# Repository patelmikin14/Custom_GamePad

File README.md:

**GamePad. End-to-End PCB Design in KiCad**

Custom Symbols · Footprint Engineering · DRC/ERC · IPC-Compliant Output · Gerber Package

A full PCB design project executed entirely in KiCad, from blank schematic through to manufacturer-ready Gerber files. Every decision was made with manufacturing constraints and industry standards in mind.

**1. Schematic design & library familiarization**
Before opening KiCad, I reviewed the full circuit on paper, mapping every signal path, power rail, and component dependency. This offline pass was intentional: it forces architectural thinking before you get distracted by the software. The schematic was then rebuilt from scratch in KiCad's Schematic Editor using standard component symbols from the pre-installed libraries and power symbols for VCC, GND, and regulated supply nets.
Every component was assigned a reference designator, value, and where applicable, a part number. Net labels replaced physical wire routing between distant schematic blocks, keeping the design readable and reconfigurable, a practice consistent with schematic documentation quality expectations outlined in IPC-2612 (schematic documentation requirements for PCBs).
Net integrity was verified at each stage, every pin was either driven, pulled, or deliberately left floating with intent documented.

**2. ERC. Catching errors at the source**
The Electrical Rules Check was run incrementally throughout schematic construction, not just at the end. Every time a new block of components was wired in, ERC was triggered immediately to surface conflicts: unconnected pins, conflicting drive types, missing power flags, duplicate reference designators. Addressing these at the component level is significantly faster than untangling a full-schematic error list at completion.
Common flags addressed included missing PWR_FLAG symbols on power nets, pin type mismatches on passive components, and unconnected input pins on logic devices. Each was resolved with an understanding of why the rule exists, not suppressed. This incremental verification approach mirrors the design review philosophy embedded in IPC-2221B (Generic Standard on Printed Board Design), which emphasizes design validation at each stage of the process rather than a single end-of-cycle check.

**3. Custom symbol creation. The OLED module**
The OLED display module required for this design was not available in the KiCad symbol libraries. Rather than approximating with a generic connector symbol, a shortcut that might cause footprint mismatches downstream, I built a custom symbol using the KiCad Symbol Editor.
Every pin was defined with the correct electrical type: power, ground, bidirectional (SDA), input (SCL), and reset. Pin electrical types directly affect ERC validation, an incorrectly typed pin can mask real drive conflicts or generate false errors that obscure genuine issues. The symbol was drawn to reflect the module's physical block structure, making the interface immediately readable to anyone reviewing the schematic.
The symbol was saved to a project-local library to ensure portability and prevent dependency on global library versions, a practice aligned with IPC-2612 documentation control guidelines.

**4. Footprint assignment, cross-referencing datasheets and distributors**
For each unique component, I cross-referenced three sources: the KiCad footprint library, the manufacturer datasheet (specifically the mechanical drawing and recommended land pattern), and distributor listings on Mouser to confirm stock and lead time. Land pattern dimensions were validated against IPC-7351C (Land Pattern Standard for SMD Components), which defines pad size, pitch tolerance, and courtyard clearance requirements for each component package type.
Footprint selection criteria applied throughout:
•	Package pitch confirmed against manufacturer soldering capability, fine-pitch components below 0.5mm were flagged for assembly risk assessment
•	Courtyard boundaries set to IPC-7351C minimums to prevent component overlap and ensure rework access
•	Through-hole vs. SMD selection weighed against assembly method, rework accessibility, and wave vs. reflow process compatibility
•	Component availability and lifecycle status checked at point of footprint assignment and not after layout
Where two parts were electrically equivalent and mechanically compatible, the lower-cost, higher-availability option was selected. A part that goes out of stock kills a production run and availability is a DFM consideration as much as geometry is.

**5. Custom footprint creation. The two non-standard parts**
Two non-standard components had no adequate footprint match in the KiCad library. Both were built from scratch using the Footprint Editor, working directly from the mechanical drawing in each component's datasheet. Land patterns were constructed in accordance with IPC-7351C guidelines, pad geometries, courtyard expansion, and fabrication layer outlines all derived from the standard's requirements for the applicable package type.
•	Copper pads: Pad size and position from the IPC-7351C recommended land pattern; SMD pads assigned to F.Cu, through-hole pads with drill diameter set to pin diameter plus IPC-recommended annular ring allowance
•	Drill holes: Diameter set per IPC-2221B minimum annular ring requirements to ensure structural integrity post-fabrication
•	Silkscreen (F.Silkscreen): Component outline and pin marker placed per IPC-7351C, offset from pad edges to remain visible post-solder
•	Courtyard (F.Courtyard): Clearance boundary set to IPC-7351C Level B minimums
•	Fabrication layer (F.Fab): True component body outline for assembly documentation and pick-and-place reference
Both footprints were verified by overlaying the 3D model and checking pad positions against the datasheet mechanical drawing before use in the layout.

**6. Manufacturer selection and constraint mapping**
The manufacturer was selected before layout began. The manufacturer's published design rules were loaded into KiCad's Board Setup and cross-checked against the minimum electrical spacing and conductor width requirements defined in IPC-2221B. Where the manufacturer's tolerances were tighter than IPC minimums, the manufacturer's values were used, the tighter constraint always governs.
•	Minimum trace width, set per manufacturer capability, validated against IPC-2221B Table 6-1 current-carrying capacity requirements for the copper weight selected
•	Minimum clearance confirmed against IPC-2221B electrical spacing tables for the board's operating voltage class
•	Minimum drill size & annular ring set to manufacturer capability, checked against IPC-2221B minimum annular ring requirements for the applicable hole class
•	Board edge clearance, copper keepout applied at the manufacturer's specified margin from Edge.Cuts
•	Copper weight selected against current load requirements using IPC-2221B trace width/current tables
All values were entered as hard constraints in KiCad so DRC would automatically flag violations during layout, no relying on manual checks after the fact.

**7. PCB layout and routing**
Component placement was tackled first, grouping by functional block (power, MCU, display, input) and positioning decoupling capacitors as close to IC power pins as physically possible. Placement decisions were made with assembly in mind: components on the same side, orientation standardised to simplify pick-and-place programming, and fine-pitch parts kept away from board edges to reduce handling risk during manufacturing practices consistent with IPC-A-610 acceptability criteria for component placement quality.
•	Power traces routed wider than signal traces, sized to current requirements using IPC-2221B trace width tables
•	Vias sized to manufacturer minimums with annular rings meeting IPC-2221B Class B requirements
•	45° routing angles used throughout, 90° corners create acid traps during etching and are explicitly flagged in IPC-2221B
•	Ground pours added on back copper to provide low-impedance return paths and reduce EMI coupling
•	I²C signal traces kept short and separated from switching power nets to reduce crosstalk
Ground pour was applied last after all routing was complete, with thermal reliefs on through-hole pads to ensure reliable solder joint formation, a direct J-STD-001 (Requirements for Soldering Electrical and Electronic Assemblies) consideration, which specifies acceptable heat transfer conditions for through-hole soldering.

**8. DRC. Validating against the standard before files leave**
The full Design Rules Check was run against the manufacturer constraints loaded in Board Setup, every copper feature on every layer validated simultaneously for clearance violations, unconnected nets, acid trap geometries, silkscreen-to-pad overlap, missing courtyard definitions, and drill-to-copper clearances.
No DRC flag was suppressed without a deliberate, documented reason. This is the point where DFM intent gets validated at the physical level and it maps directly to the pre-fabrication review process described in IPC-2221B. Silkscreen was checked to ensure no markings overlapped exposed copper pads, which would compromise solder mask inspection per IPC-A-610 visual acceptability criteria.
DRC was run multiple times as final refinements were made. A clean DRC result against real manufacturer constraints, not default KiCad tolerances was the gate condition for moving to Gerber generation.

**9. BOM generation and Gerber output**
The Bill of Materials was exported with full component attributes, reference designator, value, footprint, manufacturer part number, and quantity structured to be directly usable by a procurement or assembly team without requiring follow-up clarification.
The surface finish (HASL vs. ENIG) was selected with solderability in mind, ENIG provides a flatter, more consistent surface for fine-pitch components, which J-STD-001 identifies as a factor in achieving acceptable solder joint formation.
The full Gerber package generated:
•	F.Cu / B.Cu - front and back copper layers
•	F.Mask / B.Mask - solder mask layers defining exposed pad areas
•	F.Silkscreen / B.Silkscreen - component labels and board markings
•	Edge.Cuts - board outline for routing and panelisation
•	Drill file (.drl / Excellon format) - all via and through-hole positions and diameters
All files were verified in a Gerber viewer prior to upload, checking layer alignment, aperture definitions, and drill file integrity. The package was then submitted to the manufacturer portal where board specifications were finalised: material (FR-4), copper weight, surface finish, solder mask colour, silkscreen, and controlled impedance requirements where applicable.

**Standards Referenced:**

IPC-2221B - Generic PCB Design Standard (clearances, drill, annular ring, trace sizing)

IPC-A-610 - Acceptability of Electronic Assemblies (placement, solder joint, silkscreen criteria)

J-STD-001 - Soldering Requirements (thermal relief, paste aperture, surface finish)

IPC-2612 - Schematic Documentation Requirements

**Tools Used**

KiCad · Symbol Editor · Footprint Editor · ERC / DRC · Gerber / Excellon output · Mouser / DigiKey component validation · Gerber viewer

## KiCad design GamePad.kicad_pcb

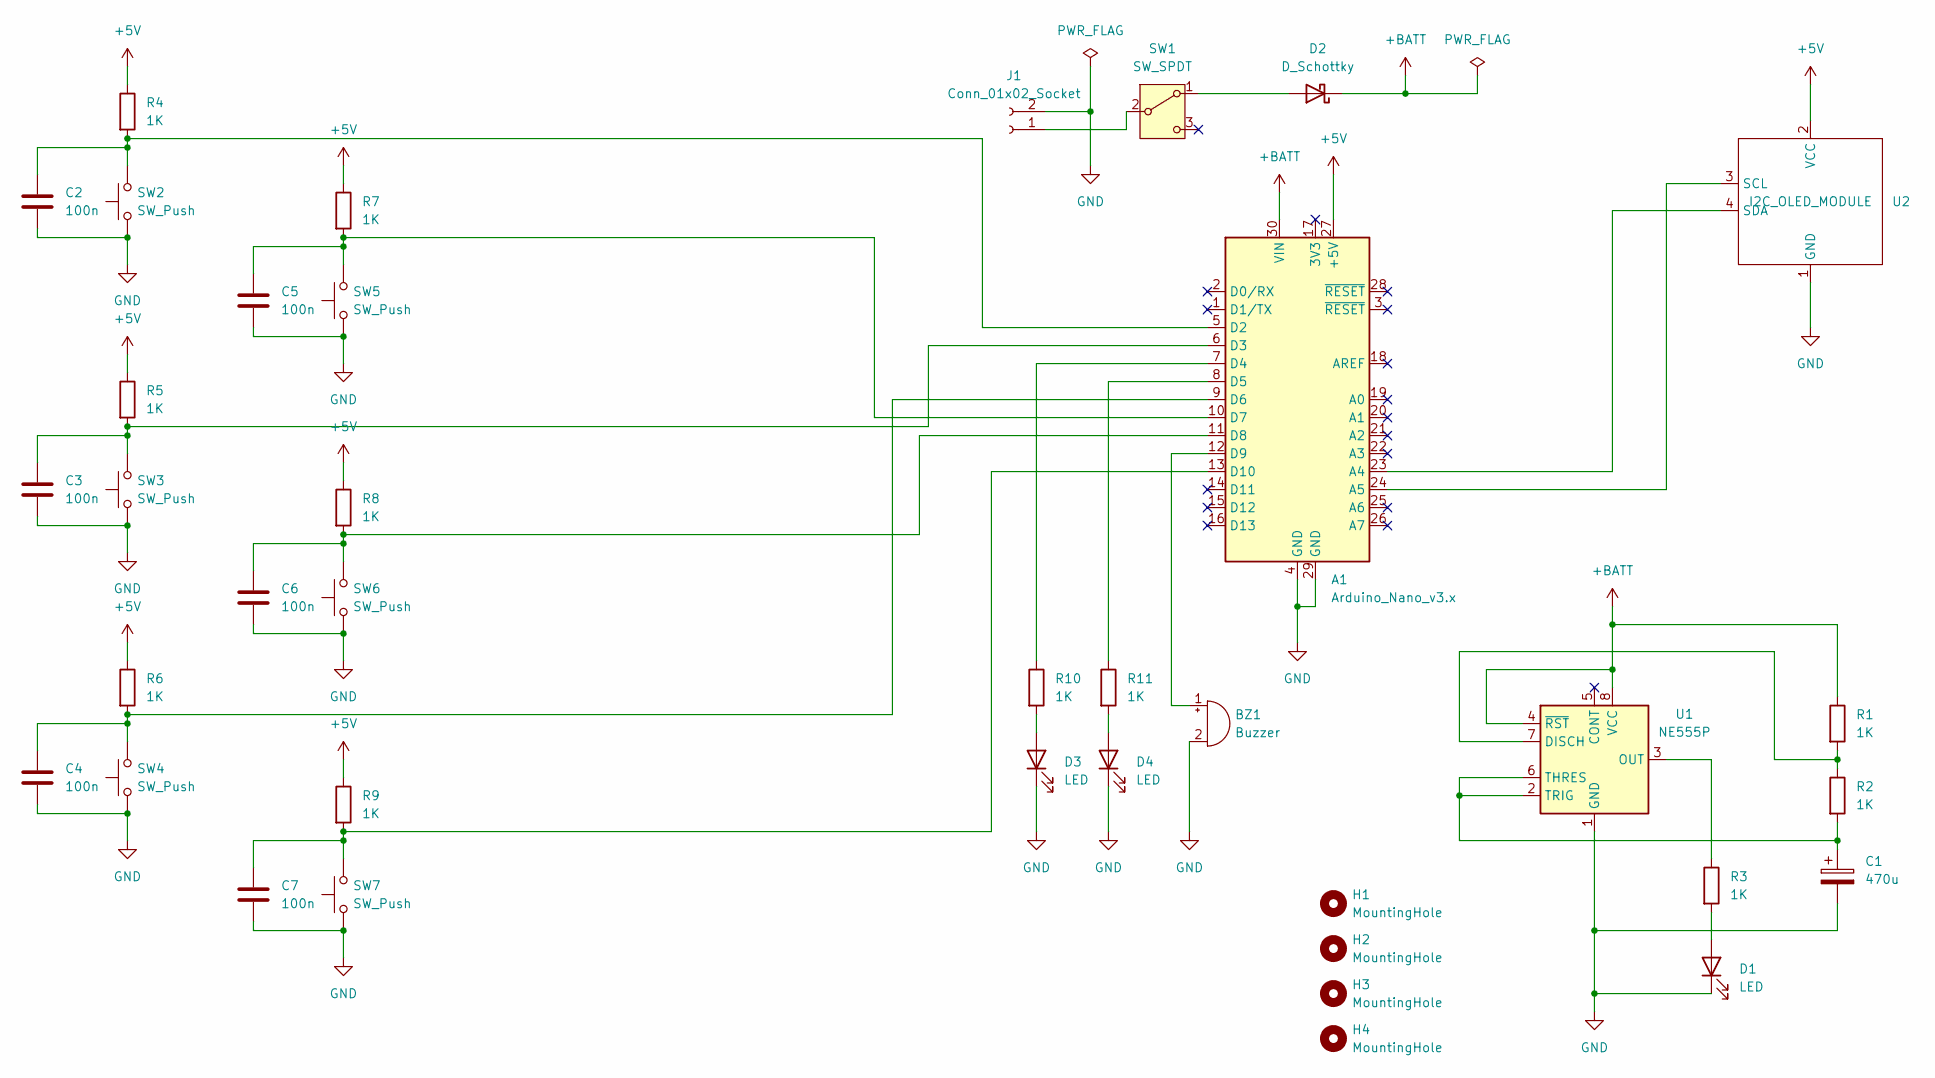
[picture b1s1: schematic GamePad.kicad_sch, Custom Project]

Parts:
A1: Arduino_Nano_v3.x; Arduino_Nano
BZ1: Buzzer; Buzzer_12x9.5RM7.6
C1: 470u; CP_Radial_D6.3mm_P2.50mm
C2, C3, C4, C5, C6, C7: 100n; C_Disc_D4.7mm_W2.5mm_P5.00mm
D1, D3, D4: LED; LED_D5.0mm
D2: D_Schottky; D_DO-35_SOD27_P7.62mm_Horizontal
H1, H2, H3, H4: MountingHole; MountingHole_2.5mm
J1: Conn_01x02_Socket; Molex_Micro-Latch_53254-0270_1x02_P2.00mm_Horizontal
R1, R2, R3, R4, R5, R6, R7, R8, R9, R10, R11: 1K; R_Axial_DIN0207_L6.3mm_D2.5mm_P7.62mm_Horizontal
SW1: SW_SPDT; spdt_slide_switch
SW2, SW3, SW4, SW5, SW6, SW7: SW_Push; SW_PUSH_6mm
U1: NE555P; DIP-8_W7.62mm
U2: I2C_OLED_MODULE; i2c_oled_module

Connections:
+5V: A1.27 (+5V), R4.1, R5.1, R6.1, R7.1, R8.1, R9.1, U2.2 (VCC)
+BATT: A1.30 (VIN), D2.1 (K), R1.1, U1.4 (~RST), U1.8 (VCC)
GND: A1.4 (GND), A1.29 (GND), BZ1.2 (-), C1.2, C2.2, C3.2, C4.2, C5.2, C6.2, C7.2, D1.1 (K), D3.1 (K), D4.1 (K), J1.2, SW2.1, SW3.1, SW4.1, SW5.1, SW6.1, SW7.1, U1.1 (GND), U2.1 (GND)
unnamed: A1.23 (A4), U2.4 (SDA)
unnamed: A1.24 (A5), U2.3 (SCL)
unnamed: A1.5 (D2), C2.1, R4.2, SW2.2
unnamed: A1.6 (D3), C3.1, R5.2, SW3.2
unnamed: A1.7 (D4), R10.1
unnamed: A1.8 (D5), R11.1
unnamed: A1.9 (D6), C4.1, R6.2, SW4.2
unnamed: A1.10 (D7), C5.1, R7.2, SW5.2
unnamed: A1.11 (D8), C6.1, R8.2, SW6.2
unnamed: A1.12 (D9), BZ1.1 (+)
unnamed: A1.13 (D10), C7.1, R9.2, SW7.2
unnamed: D1.2 (A), R3.2
unnamed: D2.2 (A), SW1.1 (A)
unnamed: D3.2 (A), R10.2
unnamed: D4.2 (A), R11.2
unnamed: J1.1, SW1.2 (B)
unnamed: R1.2, R2.1, U1.7 (DISCH)
unnamed: R3.1, U1.3 (OUT)
unnamed: C1.1, R2.2, U1.2 (TRIG), U1.6 (THRES)

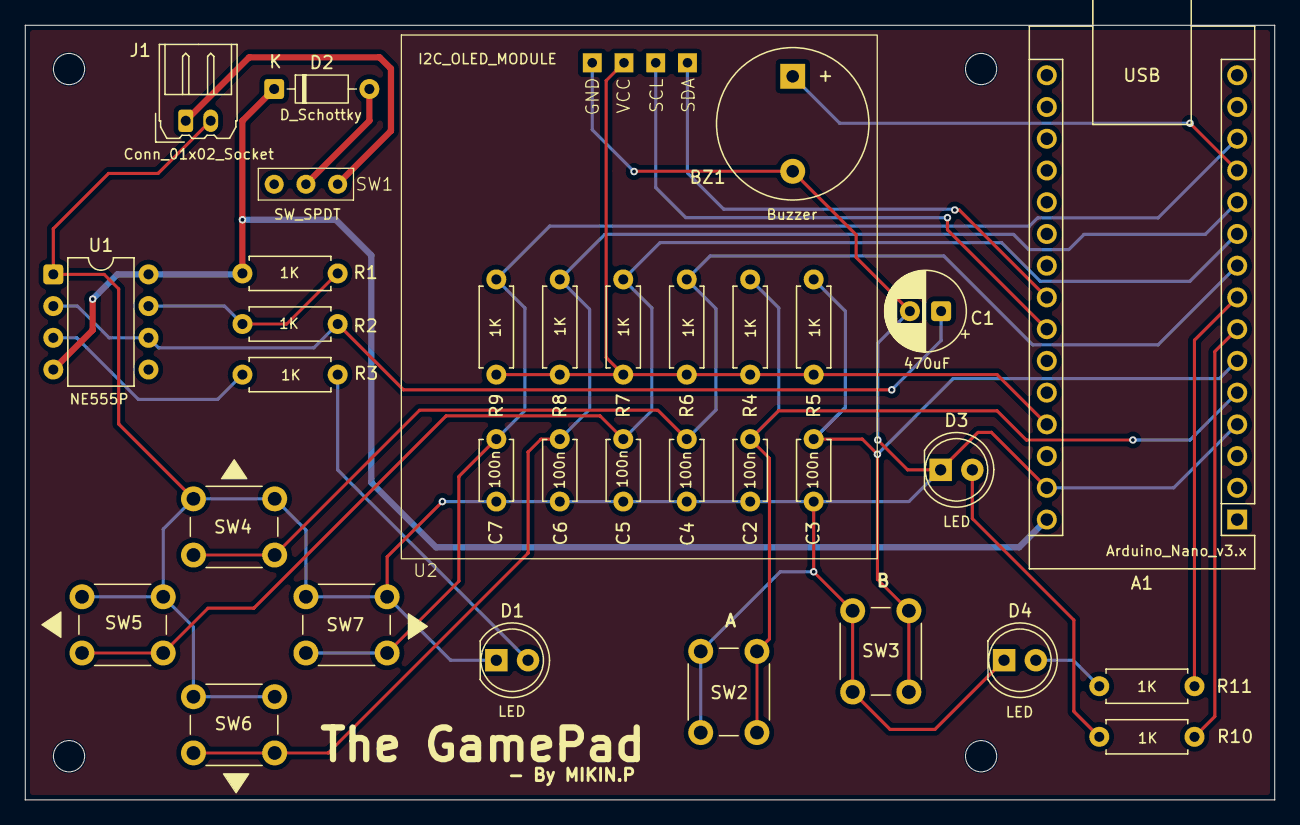
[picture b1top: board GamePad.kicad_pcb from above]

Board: 2 copper layers, 100.0 x 62.0 mm, 38 parts (0 on the bottom side), 22 nets.
